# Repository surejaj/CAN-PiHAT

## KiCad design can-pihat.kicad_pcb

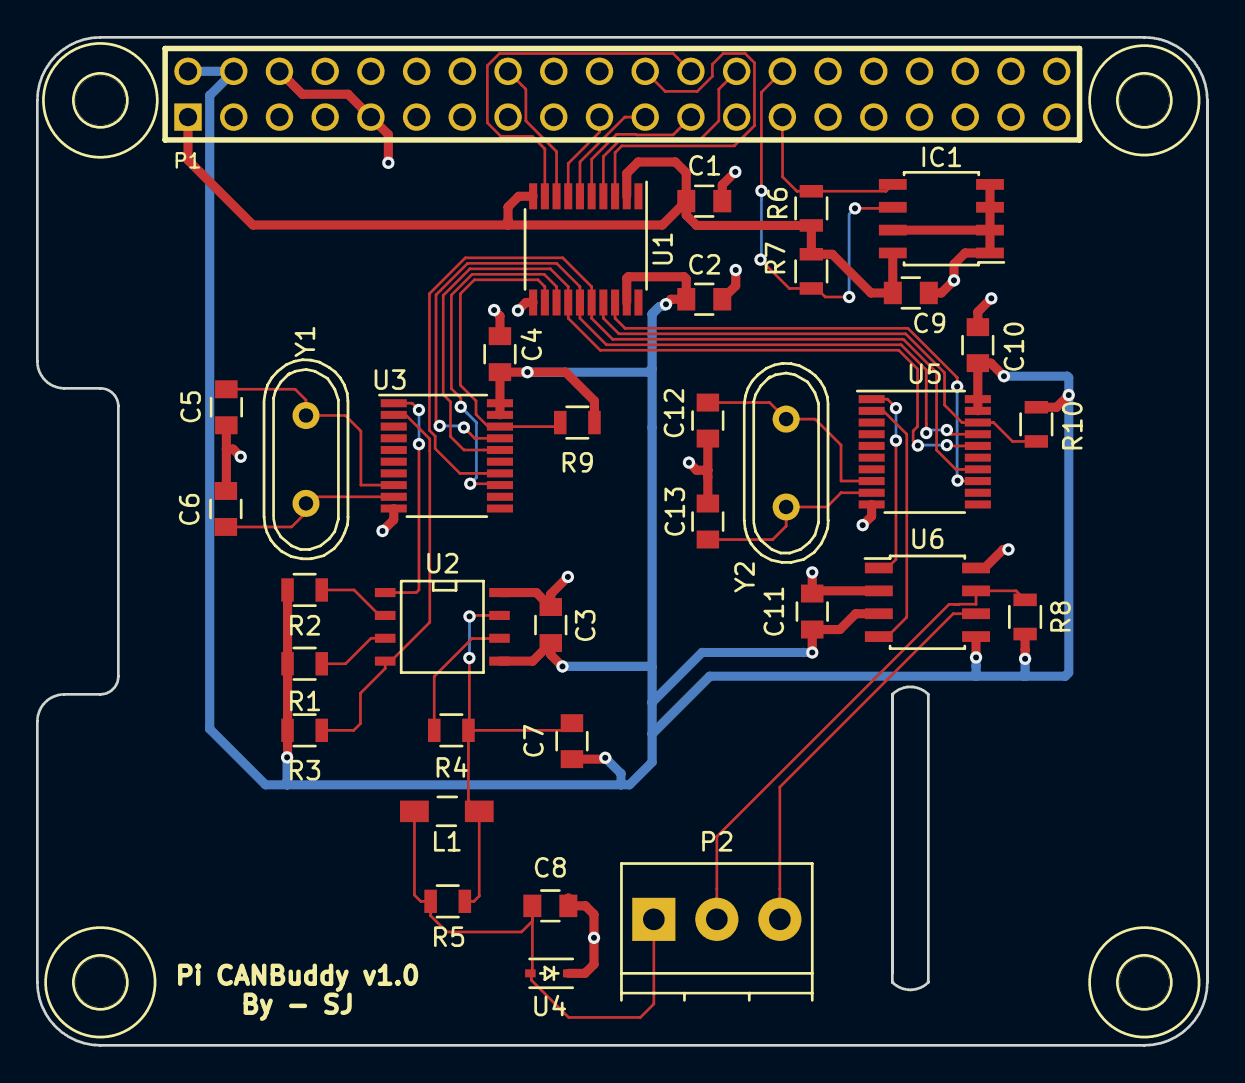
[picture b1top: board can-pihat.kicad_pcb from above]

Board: 2 copper layers, 65.0 x 56.0 mm, 40 parts (0 on the bottom side), 34 nets.

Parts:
C1, C2, C9: 0.1uF; C_0805
C3, C4, C10: 100pf; C_0805
C5, C6, C12, C13: 22pf; C_0805
C7, C8: 100pF; C_0805
C11: 100nf; C_0805
H1, H2, H3, H4: DRILL; drill3mm
H5: DRILL; ovaldrill
IC1: CAT24C32WI-GT3; SOIC-8_3.9x4.9mm_Pitch1.27mm
L1: 47uH; Choke_SMD_1206_Standard
P1: CONN_20X2; PIN_ARRAY_20X2
P2: CONN_01X03; TerminalBlock_Pheonix_PT-3.5mm_3pol
R1, R2, R9, R10: 10k; R_0805
R3: 2.7k; R_0805
R4: 6.49k; R_0805
R5: 1k; R_0805
R6, R7: 3.9K; R_0805
R8: 120; R_0805
U1: TXB0108; TSSOP-20_4.4x6.5mm_Pitch0.65mm
U2: NCV7356; SOIC-8-N
U3, U5: MCP2515; TSSOP-20_4.4x6.5mm_Pitch0.65mm
U4: PESD1LIN; SOD-323
U6: TJA1050; SOIC-8_3.9x4.9mm_Pitch1.27mm
Y1, Y2: 8Mhz; Crystal_HC49-U_Vertical

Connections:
+3V3: C1.1, C9.1, IC1.8, P1.1, R6.2, R7.2, U1.2, U1.10
+5V: C2.1, C3.1, C4.1, C7.1, C10.1, C11.1, P1.2, P1.4, R1.2, R2.2, R3.1, R8.1, R9.1, R10.1, U1.19, U2.5, U3.19, U3.20, U5.19, U5.20, U6.3, U6.5
GND: C1.2, C2.2, C3.2, C4.2, C5.2, C6.2, C8.2, C9.2, C10.2, C11.2, C12.2, C13.2, IC1.1, IC1.2, IC1.3, IC1.4, IC1.7, P1.6, P1.9, P1.25, P1.30, P1.34, P1.39, U1.11, U2.8, U3.10, U4.1, U5.10, U6.2, U6.8
HSCAN+: P2.2, R8.2, U6.7
HSCAN-: P2.3, U6.6
HSCAN_CS: R10.2, U1.17, U5.18
HSCAN_INT: U1.18, U5.13
HSCAN_RxD: U5.2, U6.4
HSCAN_TxD: U5.1, U6.1
ID_SC: IC1.6, P1.28, R7.1
ID_SD: IC1.5, P1.27, R6.1
unnamed: C5.1, U3.8, Y1.2
unnamed: C6.1, U3.9, Y1.1
unnamed: C7.2, L1.1, R4.1, R5.2, U2.7
unnamed: C12.1, U5.8, Y2.2
unnamed: C13.1, U5.9, Y2.1
unnamed: R1.1, U2.3
unnamed: R2.1, U2.2
unnamed: R4.2, U2.6
PI_HSCAN_INT: P1.22, U1.3
PI_SPI0_CE0: P1.24, U1.9
PI_SPI0_CE1: P1.26, U1.4
PI_SPI_CLK: P1.23, U1.5
PI_SPI_MISO: P1.21, U1.6
PI_SPI_MOSI: P1.19, U1.7
PI_SWCAN_INT: P1.16, U1.8
SPI_CLK: U1.16, U3.14, U5.14
SPI_MISO: U1.15, U3.17, U5.17
SPI_MOSI: U1.14, U3.16, U5.16
SWCAN: C8.1, L1.2, P2.1, R5.1, U4.2
SWCAN_CS: R9.2, U1.12, U3.18
SWCAN_INT: U1.13, U3.13
SWCAN_RxD: R3.2, U2.4, U3.2
SWCAN_TxD: U2.1, U3.1

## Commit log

2016-11-15 Adding MCP2515 with SOIC-18 footprint
2016-11-15 Updating libraries and schematic
2016-11-15 H-Sheet for SWCAN
2016-11-15 Importing HAT-EEPROM from Raspberry-Pi HAT KiCAD
2016-11-15 Adding NCV736 and PESD1LIN component libraries
2016-11-15 Importing Raspberry-Pi HAT schematic
    This commit adds Raspberry-Pi HAT related parts such as
    1. 20pin connector
    2. EEPROM
    3. Drill holes
2016-11-15 Create a new symbol for TJA1050
    New library for TJA1050. This part uses SO-8 package
2016-11-15 HSCAN: Using TJA1050 for HSCAN Transciver
    This commit contains HSCAN HSheet with MCP2515
    and TJA1050.
2016-11-15 Updating libraries with following components
    1. AT25CS32-MAHM (EEPROM for HAT)
    2. CONN_2
    3. CONN_20x2
    4. Raspberry Pi Drills
    5. Resistor
    6. Test Points
2016-11-15 Updating schematic to use new library components
2016-12-13 Added new library for part TXB0108.
2016-12-13 Adding new library part for TXB0102
2016-12-13 Fixing a typo in TXB0102 pin names.
2016-12-13 This is initial schematic for can-pihat. This version hooks up both high speed and low speed hierarchical schematics to top level schematic with various labels. Two level shifter IC's TXB0108 and TXB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
2016-12-13 Add 10k pullup resistors to both SWCAN_CS and HSCAN_CS pins. This is in reference to article:
    https://www.dorkbotpdx.org/blog/paul/better_spi_bus_design_in_3_steps
    Apparently even after disabling CS, other SPI slaves may still "hear"
    and respond to communication.
2016-12-13 Finished annotating the schematic
2016-12-14 Adding footprint for 8-VFSOP Also updating the schematic with footprints.
2017-02-06 Adding Footprints 1. Pin array 20x2 2. SO9E package 3. 3mm circular drill 4. Oval drill
2017-02-06 Few changes to schematic.
    1. Tieing WP line of eeprom to low.
    2. Removing test points from schematic.
    3. Updating the footprint of 20x2 connection
    from w_pin to Footprints:PinArray
2017-02-06 Assign pin numbers to TXB0102 and TXB0108
2017-02-06 Empty pcb file
2017-02-14 Fixing footprint issues in schematic.
    Fixed footprint pin names and numbers which
    were swapped.
    Footprint assignments.
    1. Updated footprint assignment for MCP2515.
    2. Updated SOD-323 to D_SOD-323.
    2.
2017-02-14 Initial version of Can-PiHAT PCB.
    This commit contains the 1st version
    of the board pcb. The edges are based
    on the measurements from raspberry pi
    hat mechanical spec:
    https://tinyurl.com/hc8a3t8
    Imported netlist and assigned drills
2017-03-11 Blank PCB Board
    This commit in contains an empty pcb board with raspberry
    pi hat dimensions
2017-03-18 This is an initial attempt to board layout and trace routing. The board uses two layers top side plane is 5v and bottom plane is ground. Next will be figure out better trace routes.
2017-03-31 This is the second iteration of CanPi-HAT PCB. This commit includes:
    1. Fixes the corrent footprint for CAT24C32WI
    2. Instead of power plain, a 5v trace is made in the bottom layer of
    the pcb. This trace travels underneath most of the board to provide
    power all ICs.
    3. Corrected decoupling capacitor use. The power trace will now first
    go to the decoupling capacitor and then to the respective IC.
